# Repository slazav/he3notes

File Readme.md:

Work reports and notes.
- Folders for each project.
- A tex file with all information and pictures.
- Supplementary files and folders with links from tex.

The idea is to have a complete pdf page with hyperlinks
which can be sent to any external person.

Update script put all files into SITE folder and syncronizes
it with my aalto page (https://users.aalto.fi/~zavyalv1/texts/)

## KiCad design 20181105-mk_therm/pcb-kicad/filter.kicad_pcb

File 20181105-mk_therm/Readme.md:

Simple thermometers for mK temperatures, V.Zavjalov, 2018-11-05

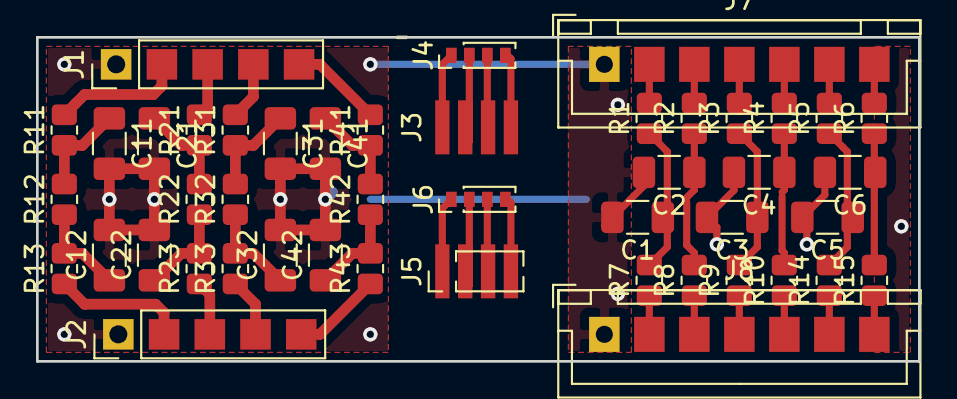
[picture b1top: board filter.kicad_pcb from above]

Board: 2 copper layers, 49.0 x 18.0 mm, 46 parts (0 on the bottom side), 43 nets.

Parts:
C1, C2, C3, C4, C5, C6, C11, C12, C21, C22, C31, C32, C41, C42: C; C_1206_3216Metric
J1, J2: Conn_01x05_Male; PinHeader_1x05_P2.54mm_Vertical
J3, J5: Conn_01x04_Male; PinHeader_1x04_P1.27mm_Vertical
J4, J6: Conn_01x04_Male; PinHeader_1x04_P1.00mm_Vertical
J7, J8: Conn_01x07_Male; JST_XH_B07B-XH-A_1x07_P2.50mm_Vertical
R1, R2, R3, R4, R5, R6, R7, R8, R9, R10, R11, R12, R13, R14, R15, R21, R22, R23, R31, R32, R33, R41, R42, R43: R; R_0805_2012Metric

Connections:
GND: C1.2, C2.2, C3.2, C4.2, C5.2, C6.2, C11.2, C12.2, C21.2, C22.2, C31.2, C32.2, C41.2, C42.2, J1.1, J2.1, J7.1, J8.1
unnamed: C1.1, R1.1, R7.2
unnamed: C2.1, R2.1, R8.2
unnamed: C3.1, R3.1, R9.2
unnamed: C4.1, R4.1, R10.2
unnamed: C5.1, R5.1, R14.2
unnamed: C6.1, R6.1, R15.2
unnamed: C11.1, R11.1, R12.2
unnamed: C12.1, R12.1, R13.2
unnamed: C21.1, R21.1, R22.2
unnamed: C22.1, R22.1, R23.2
unnamed: C31.1, R31.1, R32.2
unnamed: C32.1, R32.1, R33.2
unnamed: C41.1, R41.1, R42.2
unnamed: C42.1, R42.1, R43.2
unnamed: J1.2, R11.2
unnamed: J1.3, R21.2
unnamed: J1.4, R31.2
unnamed: J1.5, R41.2
unnamed: J2.2, R13.1
unnamed: J2.3, R23.1
unnamed: J2.4, R33.1
unnamed: J2.5, R43.1
unnamed: J3.1, J4.1
unnamed: J3.2, J4.2
unnamed: J3.3, J4.3
unnamed: J3.4, J4.4
unnamed: J5.1, J6.1
unnamed: J5.2, J6.2
unnamed: J5.3, J6.3
unnamed: J5.4, J6.4
unnamed: J7.2, R1.2
unnamed: J7.3, R2.2
unnamed: J7.4, R3.2
unnamed: J7.5, R4.2
unnamed: J7.6, R5.2
unnamed: J7.7, R6.2
unnamed: J8.2, R7.1
unnamed: J8.3, R8.1
unnamed: J8.4, R9.1
unnamed: J8.5, R10.1
unnamed: J8.6, R14.1
unnamed: J8.7, R15.1

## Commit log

2018-11-05 add 20181105-mk_therm
2018-11-05 add kicad files
2018-11-05 update 20181105-mk_therm
2018-11-06 move some common Makefile things to Makefile.inc
2018-11-06 add brands.tex file
2018-11-15 rearrange files; add SITE update script
2018-11-15 add 2016-nmrcell1, 2018-bncclamps
